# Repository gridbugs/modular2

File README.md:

# Modular 2

A modular synthesizer, where modules are designed as close to bare PCBs as is
practical/safe. This is the spiritual successor to the [briefcase modular
synthesizer](https://github.com/gridbugs/briefcase-synth/).

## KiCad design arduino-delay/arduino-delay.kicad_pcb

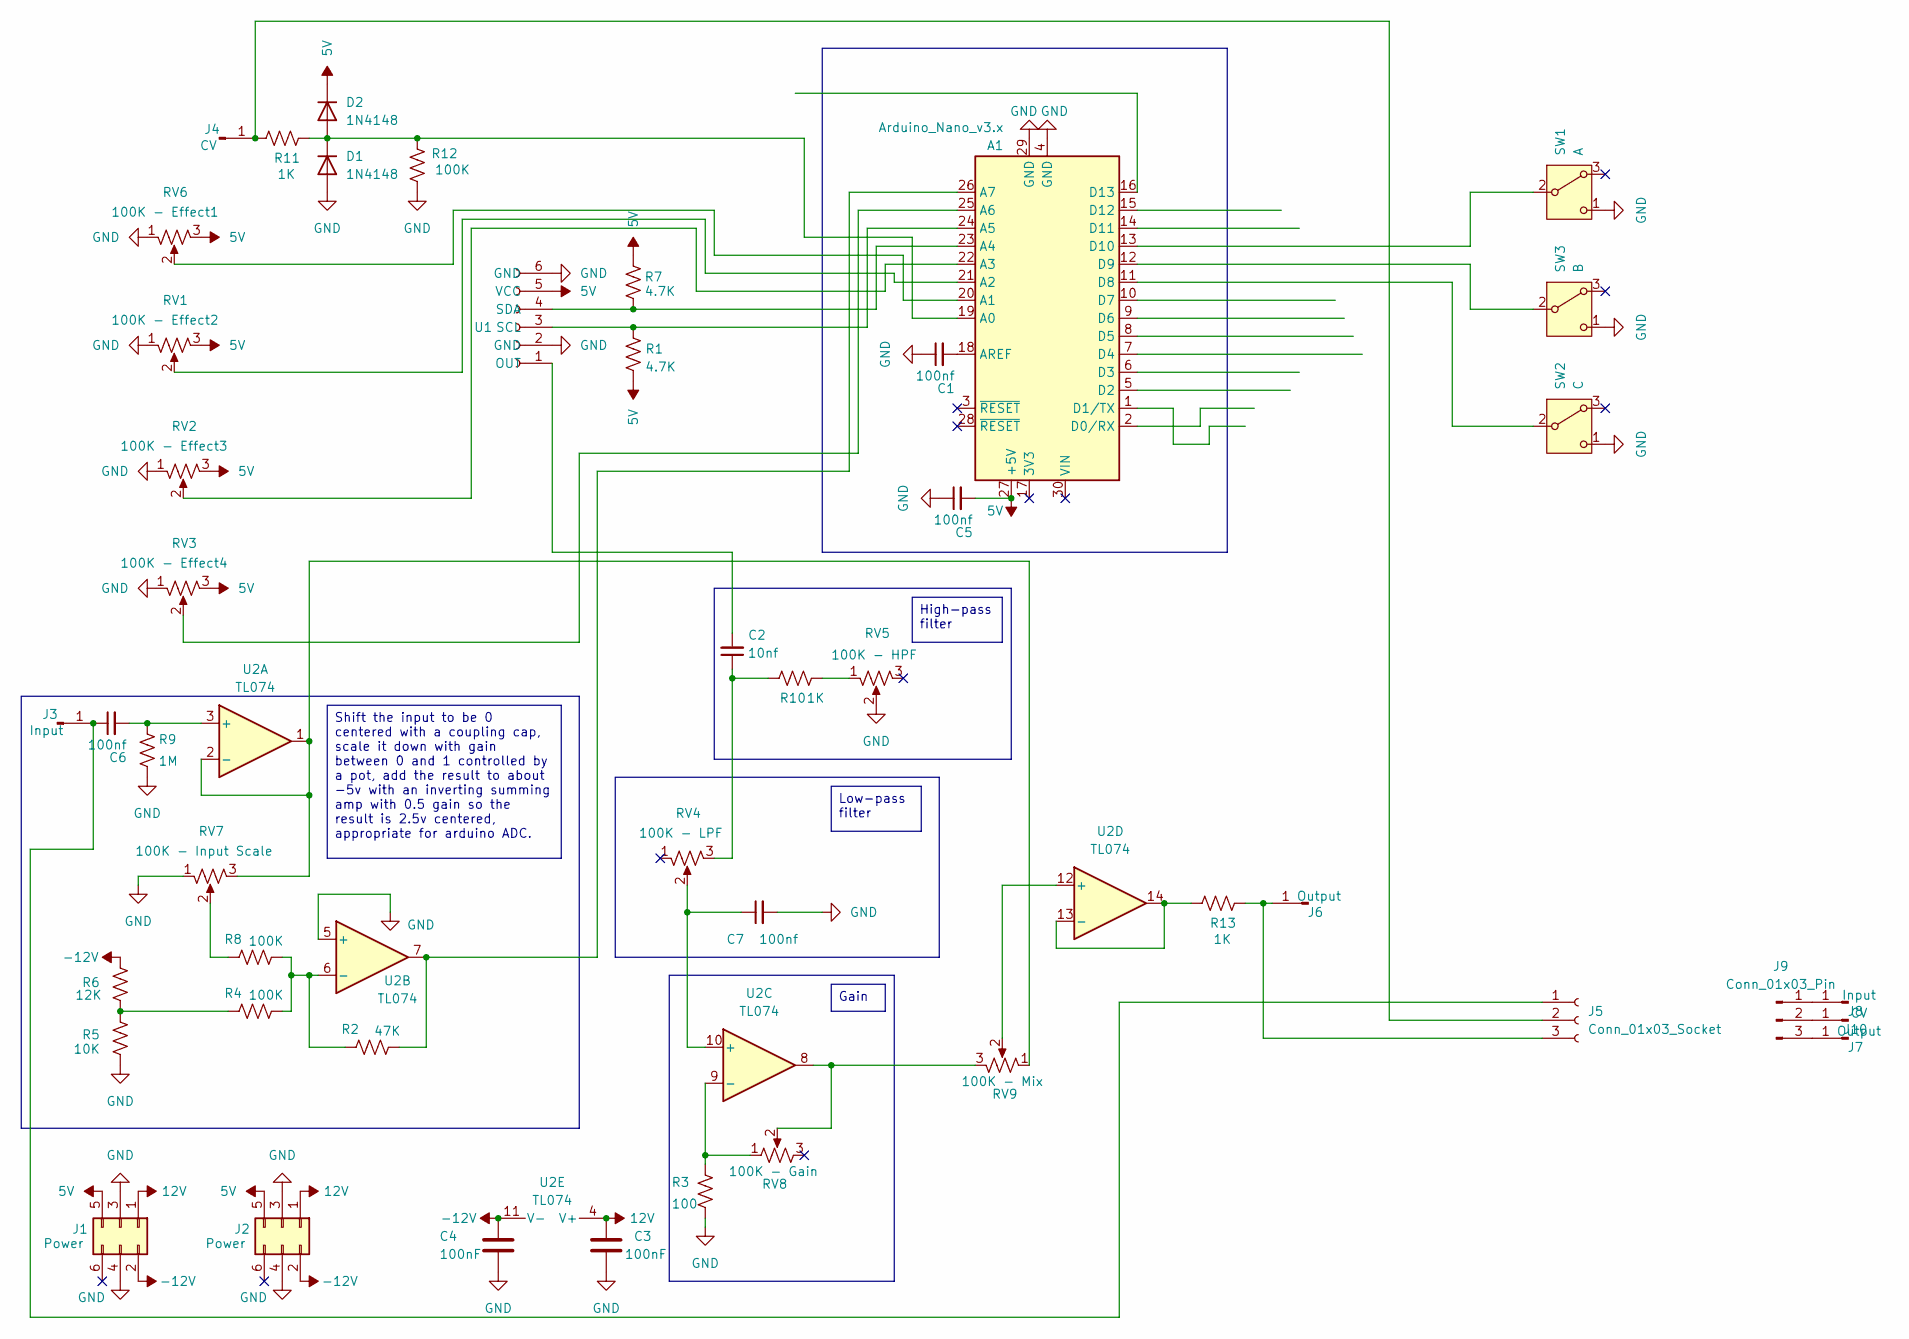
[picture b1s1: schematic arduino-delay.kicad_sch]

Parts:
A1: Arduino_Nano_v3.x; Arduino_Nano_sockets
C1, C5, C6, C7: 100nf; C_Disc_D4.3mm_W1.9mm_P5.00mm
C2: 10nf; C_Disc_D4.3mm_W1.9mm_P5.00mm
C3, C4: 100nF; C_Disc_D4.3mm_W1.9mm_P5.00mm
D1, D2: 1N4148; D_DO-35_SOD27_P7.62mm_Horizontal
J1, J2: Power; IDC-Header_2x03_P2.54mm_Vertical
J3, J8: Input; banana-jack
J4, J10: CV; banana-jack
J5: Conn_01x03_Socket; PinSocket_1x03_P2.54mm_Vertical
J6, J7: Output; banana-jack
J9: Conn_01x03_Pin; PinHeader_1x03_P2.54mm_Vertical
R1, R7: 4.7K; R_Axial_DIN0207_L6.3mm_D2.5mm_P10.16mm_Horizontal
R2: 47K; R_Axial_DIN0207_L6.3mm_D2.5mm_P10.16mm_Horizontal
R3: 100; R_Axial_DIN0207_L6.3mm_D2.5mm_P10.16mm_Horizontal
R4, R8, R12: 100K; R_Axial_DIN0207_L6.3mm_D2.5mm_P10.16mm_Horizontal
R5: 10K; R_Axial_DIN0207_L6.3mm_D2.5mm_P10.16mm_Horizontal
R6: 12K; R_Axial_DIN0207_L6.3mm_D2.5mm_P10.16mm_Horizontal
R9: 1M; R_Axial_DIN0207_L6.3mm_D2.5mm_P10.16mm_Horizontal
R10, R11, R13: 1K; R_Axial_DIN0207_L6.3mm_D2.5mm_P10.16mm_Horizontal
RV1: 100K - Effect2; Potentiometer_Alps_RK09K_Single_Vertical - knob padding
RV2: 100K - Effect3; Potentiometer_Alps_RK09K_Single_Vertical - knob padding
RV3: 100K - Effect4; Potentiometer_Alps_RK09K_Single_Vertical - knob padding
RV4: 100K - LPF; Potentiometer_Alps_RK09K_Single_Vertical - knob padding
RV5: 100K - HPF; Potentiometer_Alps_RK09K_Single_Vertical - knob padding
RV6: 100K - Effect1; Potentiometer_Alps_RK09K_Single_Vertical - knob padding
RV7: 100K - Input Scale; Potentiometer_Alps_RK09K_Single_Vertical - knob padding
RV8: 100K - Gain; Potentiometer_Alps_RK09K_Single_Vertical - knob padding
RV9: 100K - Mix; Potentiometer_Alps_RK09K_Single_Vertical - knob padding
SW1: A; switch1
SW2: C; switch1
SW3: B; switch1
U1: mcp4725_breakout
U2: TL074; DIP-14_W7.62mm_Socket

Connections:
5V: A1.27 (+5V), C5.2, D2.1 (K), J1.5, J2.5, R1.2, R7.2, RV1.3, RV2.3, RV3.3, RV6.3, U1.5 (VCC)
12V: C3.2, J1.1, J2.1, U2.4 (V+)
-12V: C4.2, J1.2, J2.2, R6.2, U2.11 (V-)
GND: A1.4 (GND), A1.29 (GND), C1.1, C3.1, C4.1, C5.1, C7.2, D1.2 (A), J1.3, J1.4, J2.3, J2.4, R3.1, R5.1, R9.2, R12.2, RV1.1, RV2.1, RV3.1, RV5.2, RV6.1, RV7.1, SW1.1 (C), SW2.1 (C), SW3.1 (C), U1.2 (GND), U1.6 (GND), U2.5 (+)
unnamed: A1.19 (A0), D1.1 (K), D2.2 (A), R11.1, R12.1
unnamed: A1.20 (A1), RV6.2
unnamed: A1.21 (A2), RV1.2
unnamed: A1.22 (A3), RV2.2
unnamed: A1.23 (A4), R7.1, U1.4 (SDA)
unnamed: A1.24 (A5), R1.1, U1.3 (SCL)
unnamed: A1.25 (A6), RV3.2
unnamed: A1.26 (A7), R2.2, U2.7
unnamed: A1.18 (AREF), C1.2
unnamed: A1.11 (D8), SW2.2 (B)
unnamed: A1.12 (D9), SW3.2 (B)
unnamed: A1.13 (D10), SW1.2 (B)
unnamed: C2.1, R10.2, RV4.3
unnamed: C6.1, J3.1, J5.1
unnamed: J4.1, J5.2, R11.2
unnamed: J5.3, J6.1, R13.1
unnamed: J7.1, J9.3
unnamed: J8.1, J9.1
unnamed: J9.2, J10.1
unnamed: R4.1, R5.2, R6.1
unnamed: R8.1, RV7.2
unnamed: R10.1, RV5.1
unnamed: RV8.2, RV9.3, U2.8
unnamed: C2.2, U1.1 (OUT)
unnamed: C6.2, R9.1, U2.3 (+)
unnamed: RV7.3, RV9.1, U2.1, U2.2 (-)
unnamed: R2.1, R4.2, R8.2, U2.6 (-)
unnamed: C7.1, RV4.2, U2.10 (+)
unnamed: R3.2, RV8.1, U2.9 (-)
unnamed: RV9.2, U2.12 (+)
unnamed: R13.2, U2.13 (-), U2.14

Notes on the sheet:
Shift the input to be 0 centered with a coupling cap, scale it down with gain between 0 and 1 controlled by a pot, add the result to about -5v with an inverting summing amp with 0.5 gain so the result is 2.5v centered, appropriate for arduino ADC.
High-pass filter
Gain
Low-pass filter

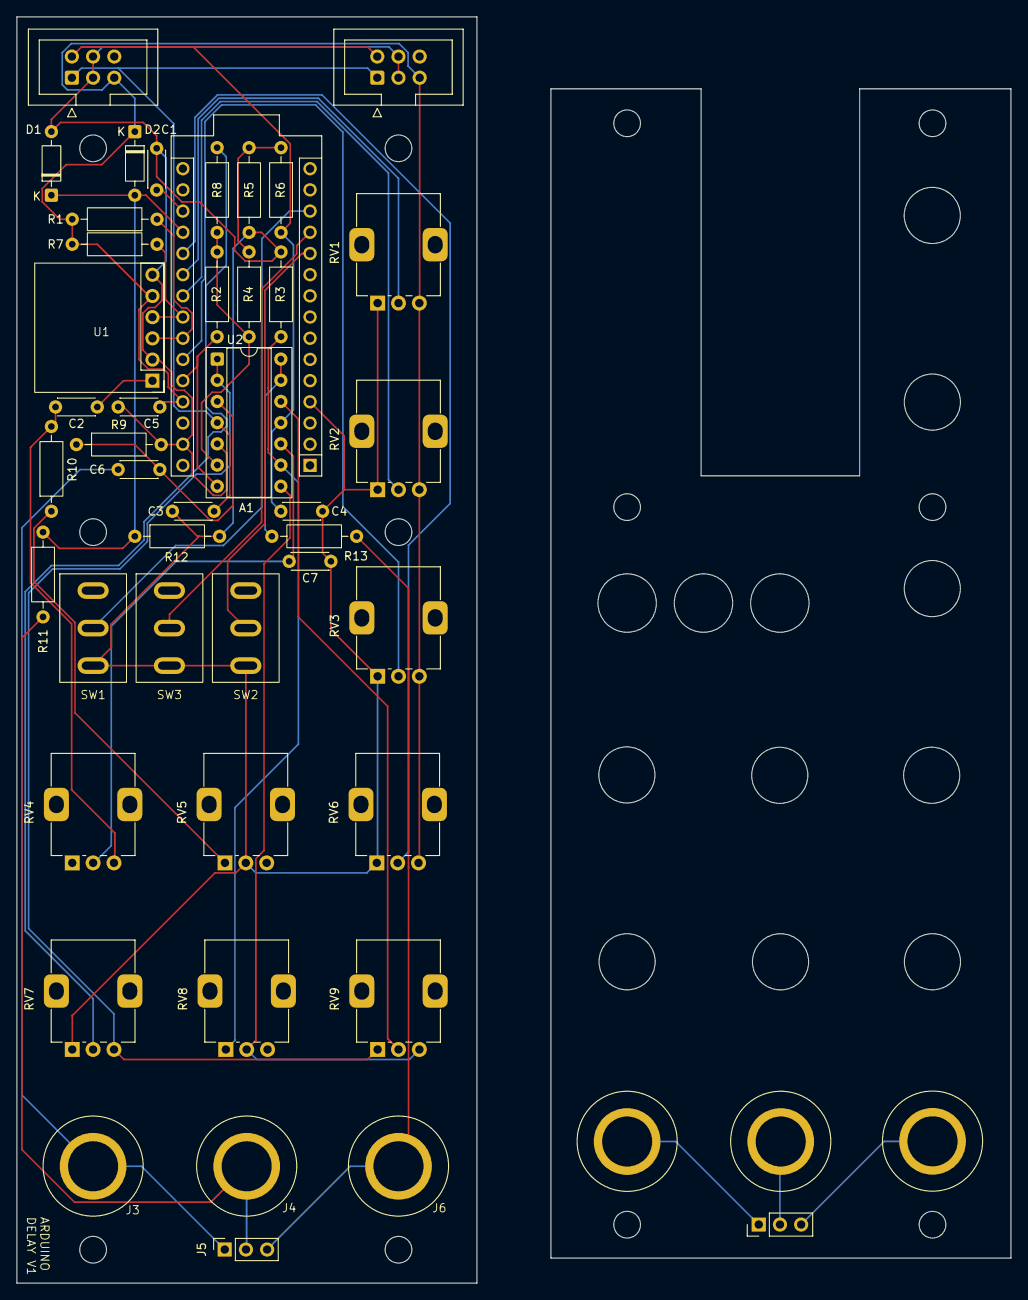
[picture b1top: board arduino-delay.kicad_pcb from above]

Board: 2 copper layers, 55.1 x 151.8 mm, 47 parts (0 on the bottom side), 35 nets.

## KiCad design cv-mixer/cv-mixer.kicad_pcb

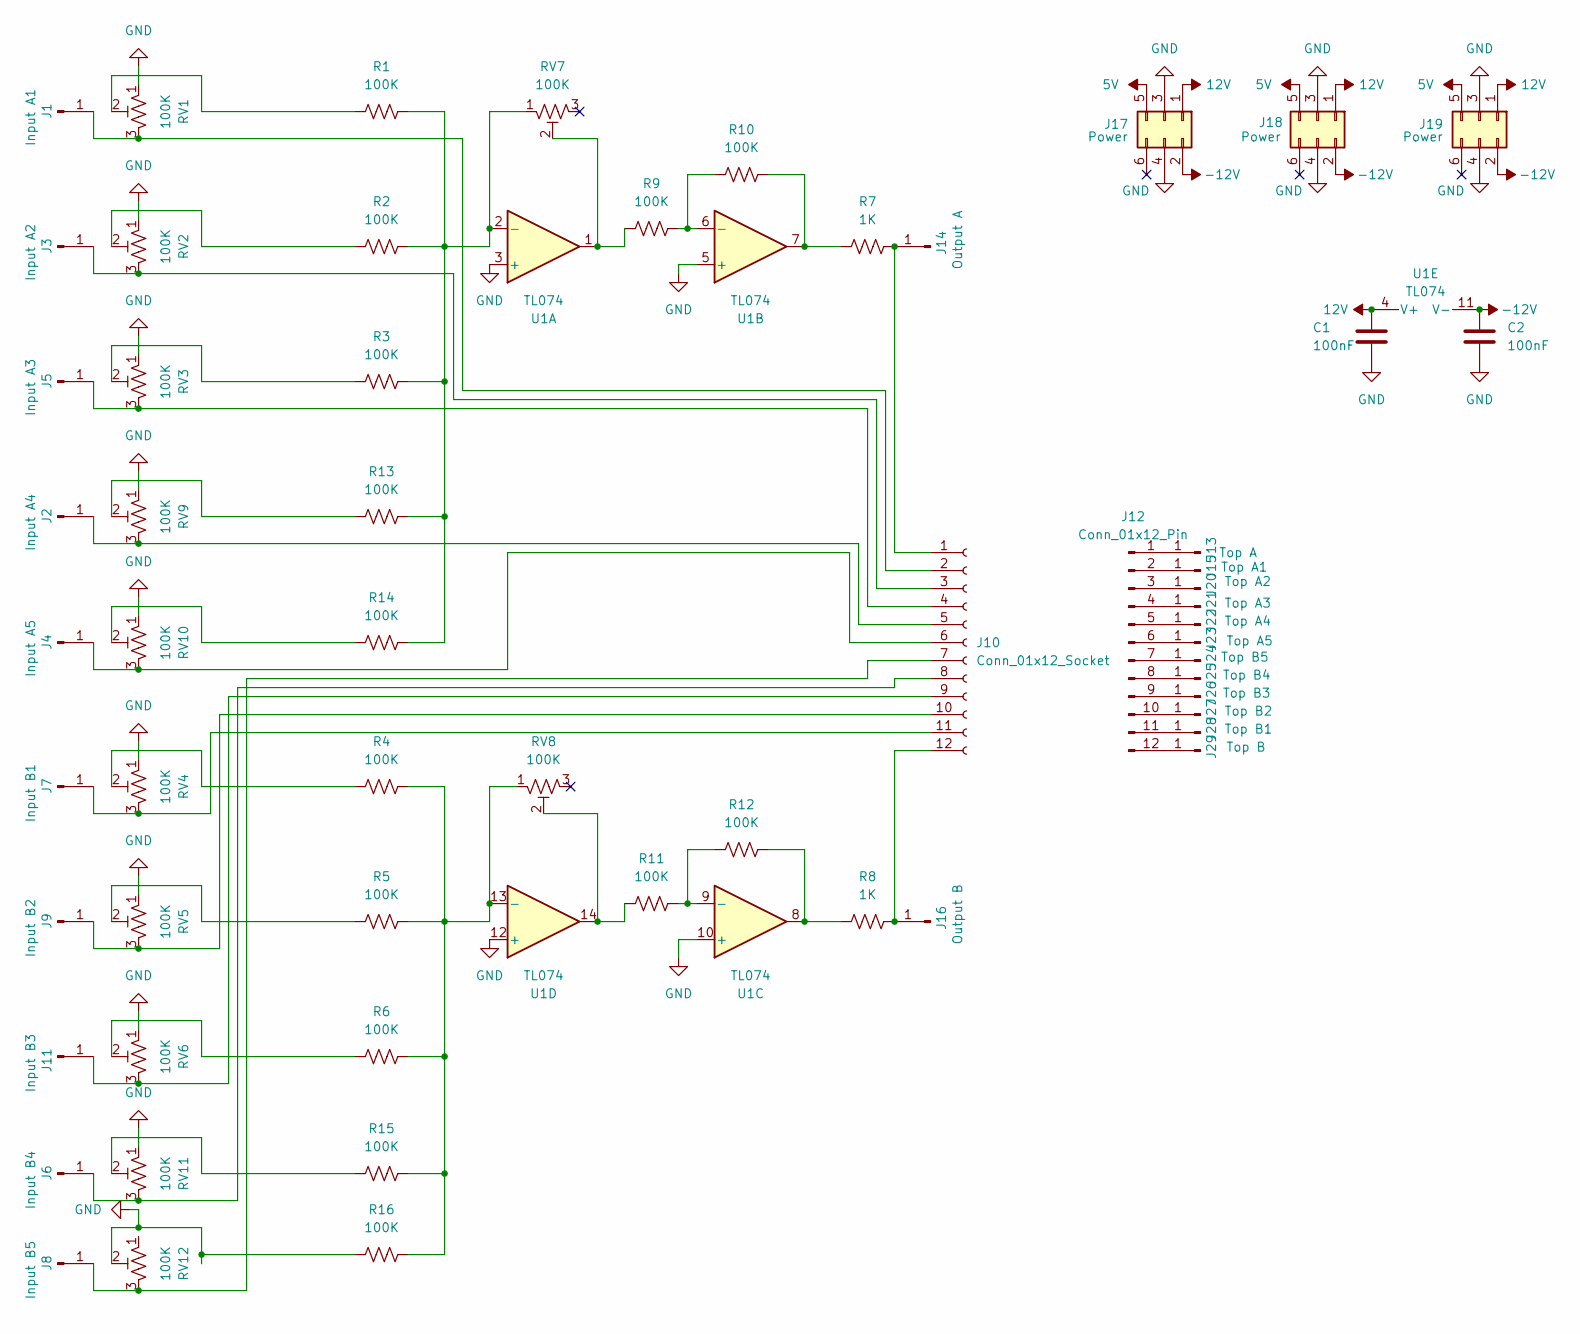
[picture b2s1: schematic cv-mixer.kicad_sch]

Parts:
C1, C2: 100nF; C_Disc_D4.3mm_W1.9mm_P5.00mm
J1: Input A1; banana-jack
J2: Input A4; banana-jack
J3: Input A2; banana-jack
J4: Input A5; banana-jack
J5: Input A3; banana-jack
J6: Input B4; banana-jack
J7: Input B1; banana-jack
J8: Input B5; banana-jack
J9: Input B2; banana-jack
J10: Conn_01x12_Socket; PinSocket_1x12_P2.54mm_Vertical
J11: Input B3; banana-jack
J12: Conn_01x12_Pin; PinHeader_1x12_P2.54mm_Vertical
J13: Top A; banana-jack
J14: Output A; banana-jack
J15: Top A1; banana-jack
J16: Output B; banana-jack
J17, J18, J19: Power; IDC-Header_2x03_P2.54mm_Vertical
J20: Top A2; banana-jack
J21: Top A3; banana-jack
J22: Top A4; banana-jack
J23: Top A5; banana-jack
J24: Top B5; banana-jack
J25: Top B4; banana-jack
J26: Top B3; banana-jack
J27: Top B2; banana-jack
J28: Top B1; banana-jack
J29: Top B; banana-jack
R1, R2, R3, R4, R5, R6, R9, R10, R11, R12, R13, R14, R15, R16: 100K; R_Axial_DIN0207_L6.3mm_D2.5mm_P10.16mm_Horizontal
R7, R8: 1K; R_Axial_DIN0207_L6.3mm_D2.5mm_P10.16mm_Horizontal
RV1, RV2, RV3, RV4, RV5, RV6, RV7, RV8, RV9, RV10, RV11, RV12: 100K; Potentiometer_Alps_RK09K_Single_Vertical - knob padding
U1: TL074; DIP-14_W7.62mm_Socket

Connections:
5V: J17.5, J18.5, J19.5
12V: C1.2, J17.1, J18.1, J19.1, U1.4 (V+)
-12V: C2.2, J17.2, J18.2, J19.2, U1.11 (V-)
GND: C1.1, C2.1, J17.3, J17.4, J18.3, J18.4, J19.3, J19.4, R16.1, RV1.1, RV2.1, RV3.1, RV4.1, RV5.1, RV6.1, RV9.1, RV10.1, RV11.1, RV12.2, U1.3 (+), U1.5 (+), U1.10 (+), U1.12 (+)
unnamed: J1.1, J10.2, RV1.3
unnamed: J10.1, J14.1, R7.2
unnamed: J3.1, J10.3, RV2.3
unnamed: J5.1, J10.4, RV3.3
unnamed: J2.1, J10.5, RV9.3
unnamed: J4.1, J10.6, RV10.3
unnamed: J8.1, J10.7, RV12.3
unnamed: J6.1, J10.8, RV11.3
unnamed: J10.9, J11.1, RV6.3
unnamed: J9.1, J10.10, RV5.3
unnamed: J7.1, J10.11, RV4.3
unnamed: J10.12, J16.1, R8.2
unnamed: J12.1, J13.1
unnamed: J12.2, J15.1
unnamed: J12.3, J20.1
unnamed: J12.4, J21.1
unnamed: J12.5, J22.1
unnamed: J12.6, J23.1
unnamed: J12.7, J24.1
unnamed: J12.8, J25.1
unnamed: J12.9, J26.1
unnamed: J12.10, J27.1
unnamed: J12.11, J28.1
unnamed: J12.12, J29.1
unnamed: R1.1, RV1.2
unnamed: R2.1, RV2.2
unnamed: R3.1, RV3.2
unnamed: R4.1, RV4.2
unnamed: R5.1, RV5.2
unnamed: R6.1, RV6.2
unnamed: R9.1, RV7.2, U1.1
unnamed: R7.1, R10.2, U1.7
unnamed: R11.1, RV8.2, U1.14
unnamed: R8.1, R12.2, U1.8
unnamed: R13.1, RV9.2
unnamed: R14.1, RV10.2
unnamed: R15.1, RV11.2
unnamed: R1.2, R2.2, R3.2, R13.2, R14.2, RV7.1, U1.2 (-)
unnamed: R9.2, R10.1, U1.6 (-)
unnamed: R11.2, R12.1, U1.9 (-)
unnamed: R4.2, R5.2, R6.2, R15.2, R16.2, RV8.1, U1.13 (-)

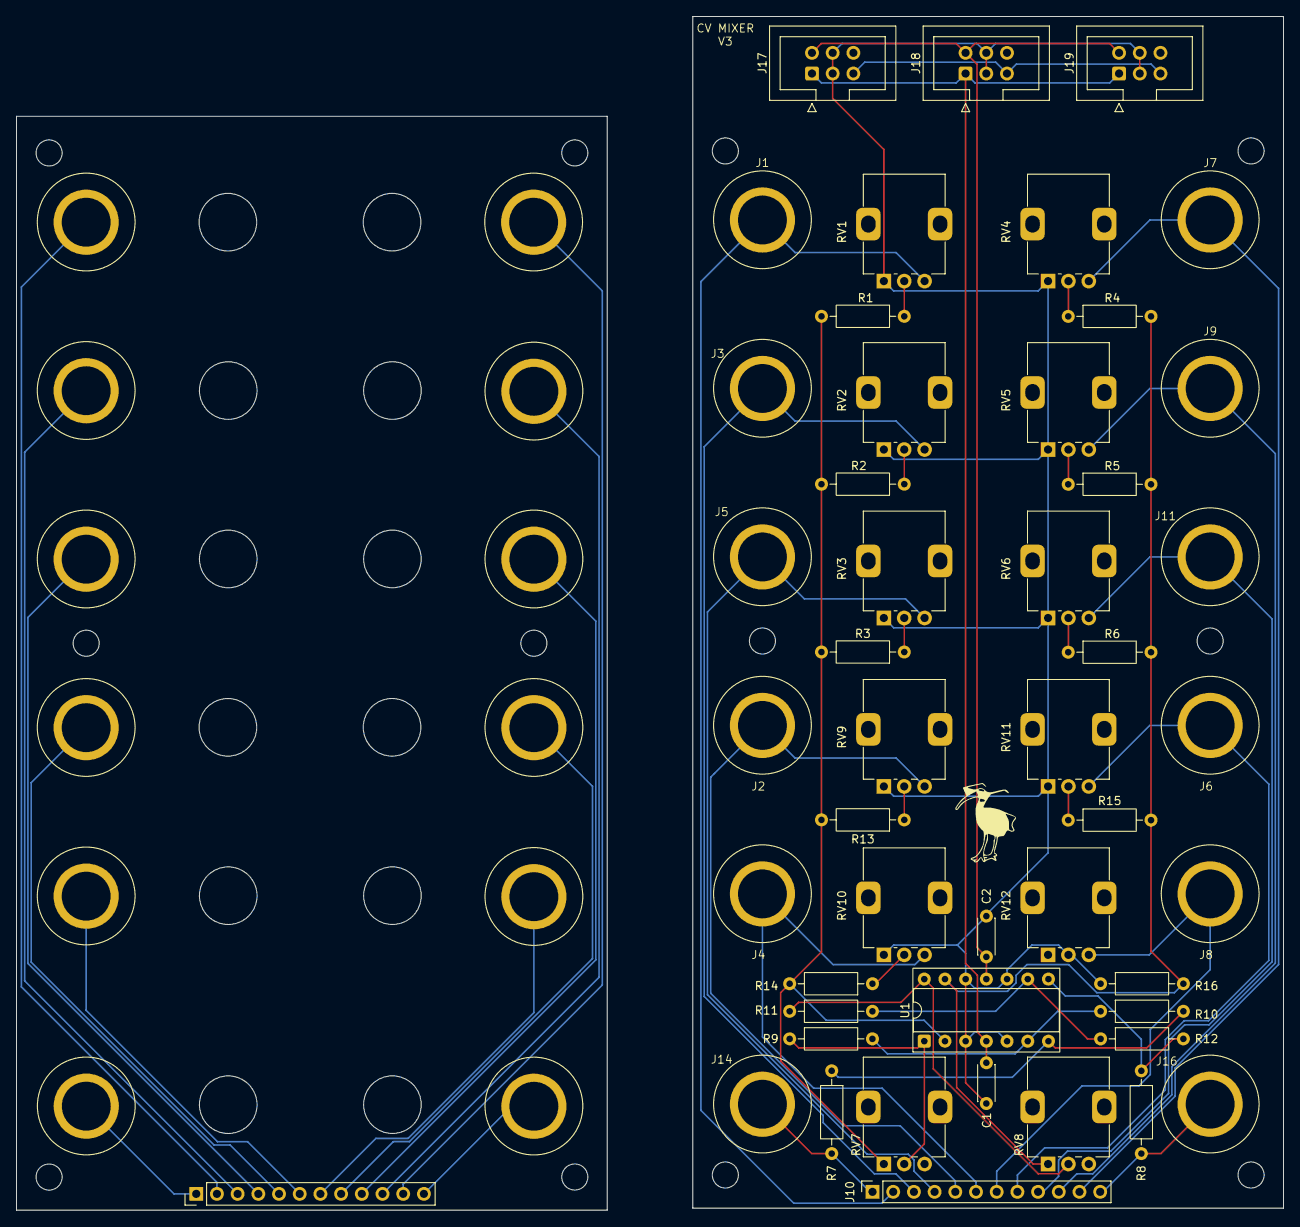
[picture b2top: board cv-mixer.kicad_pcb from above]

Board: 2 copper layers, 155.5 x 146.5 mm, 60 parts (0 on the bottom side), 45 nets.

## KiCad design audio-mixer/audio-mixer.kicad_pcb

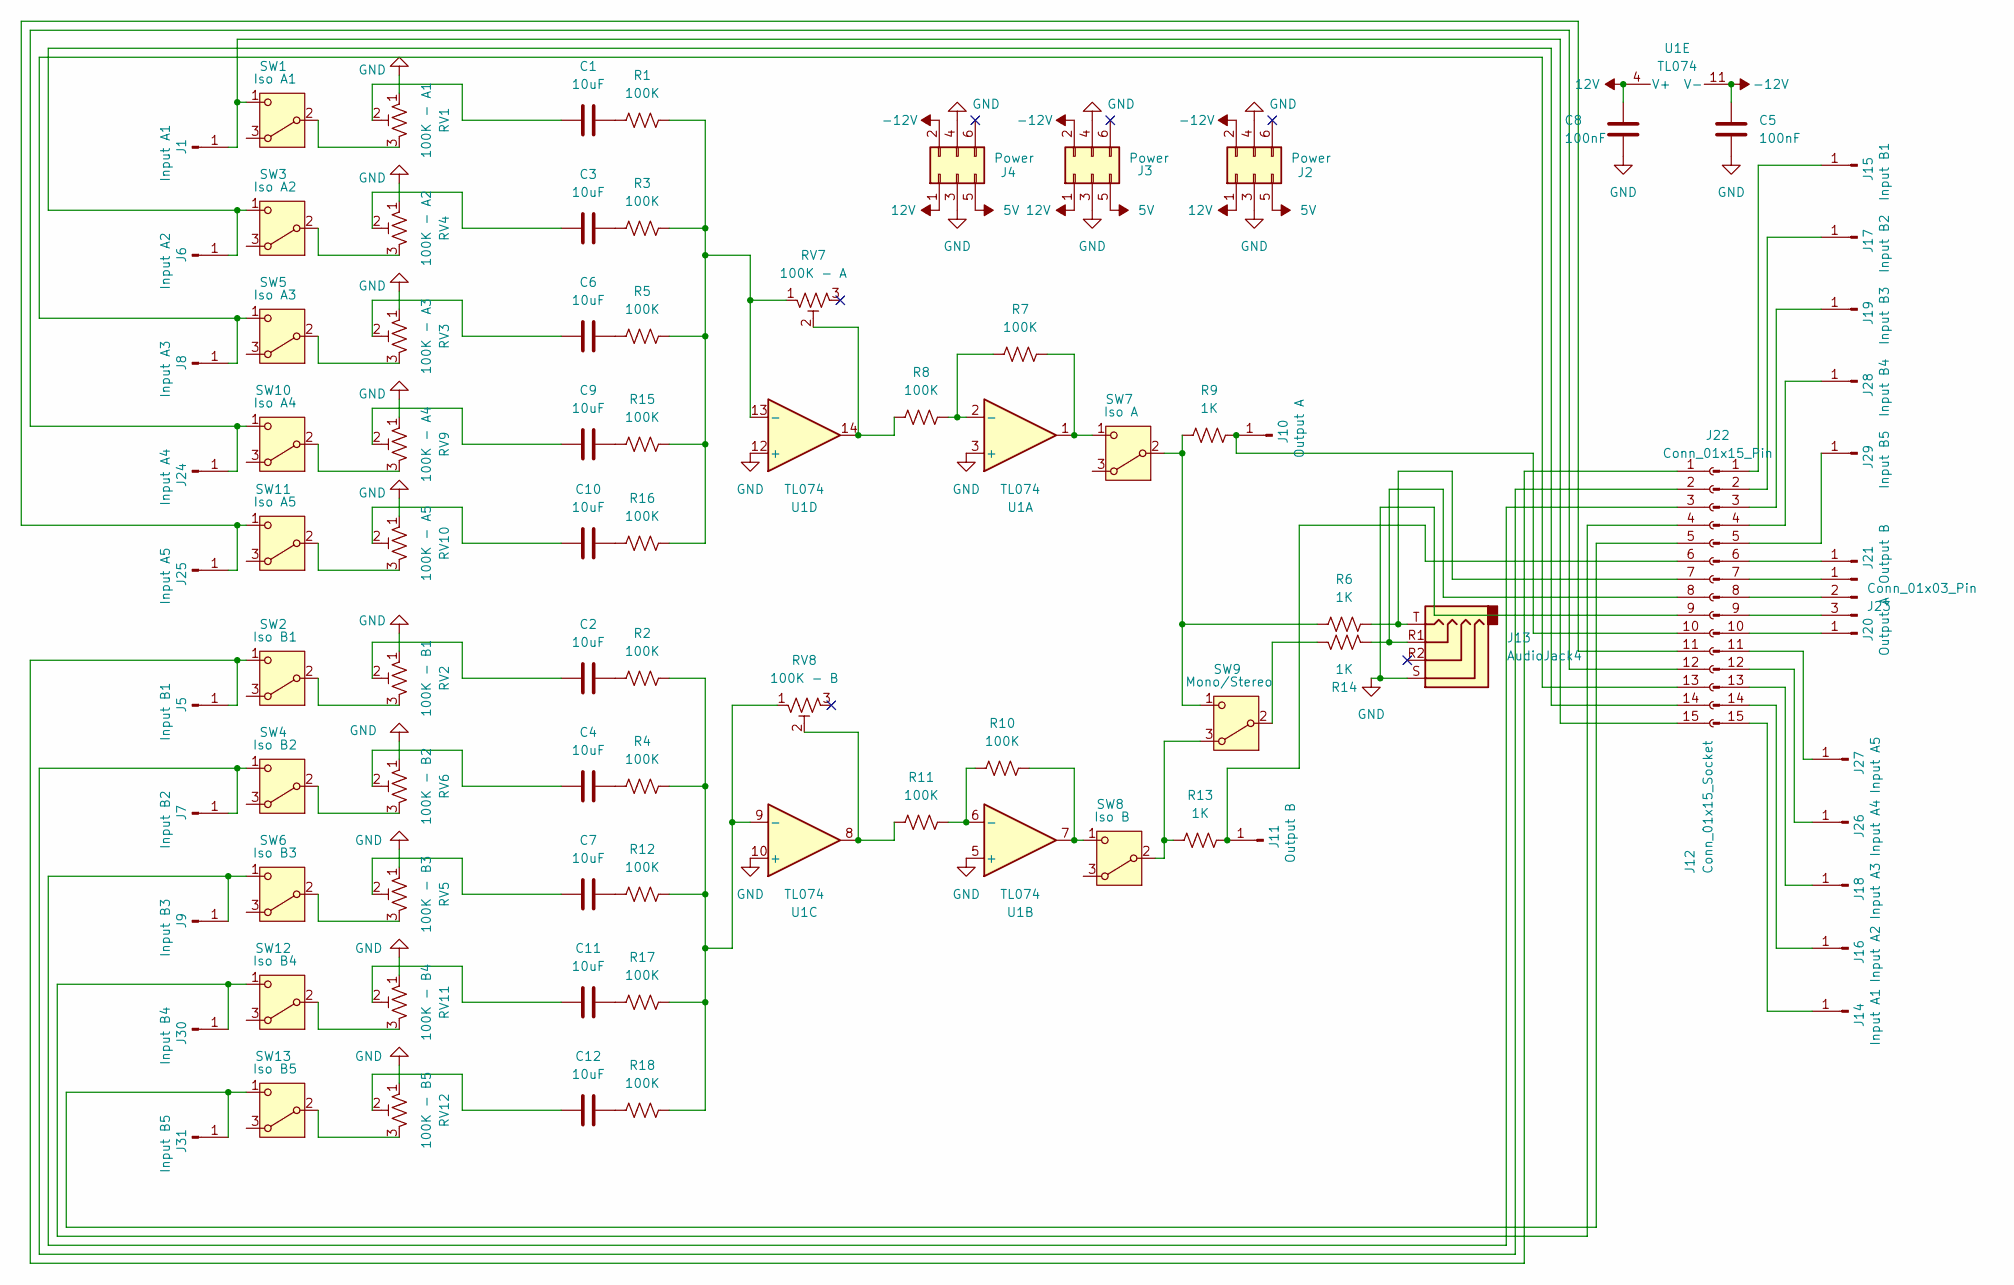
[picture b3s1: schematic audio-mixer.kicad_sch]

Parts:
C1, C2, C3, C4, C6, C7, C9, C10, C11, C12: 10uF; C_Disc_D4.3mm_W1.9mm_P5.00mm
C5, C8: 100nF; C_Disc_D4.3mm_W1.9mm_P5.00mm
J1, J14: Input A1; banana-jack
J2, J3, J4: Power; IDC-Header_2x03_P2.54mm_Vertical
J5, J15: Input B1; banana-jack
J6, J16: Input A2; banana-jack
J7, J17: Input B2; banana-jack
J8, J18: Input A3; banana-jack
J9, J19: Input B3; banana-jack
J10, J20: Output A; banana-jack
J11, J21: Output B; banana-jack
J12: Conn_01x15_Socket; PinSocket_1x15_P2.54mm_Vertical
J13: AudioJack4; audio jack breakout
J22: Conn_01x15_Pin; PinHeader_1x15_P2.54mm_Vertical
J23: Conn_01x03_Pin; PinHeader_1x03_P2.54mm_Vertical
J24, J26: Input A4; banana-jack
J25, J27: Input A5; banana-jack
J28, J30: Input B4; banana-jack
J29, J31: Input B5; banana-jack
R1, R2, R3, R4, R5, R7, R8, R10, R11, R12, R15, R16, R17, R18: 100K; R_Axial_DIN0207_L6.3mm_D2.5mm_P10.16mm_Horizontal
R6, R9, R13, R14: 1K; R_Axial_DIN0207_L6.3mm_D2.5mm_P10.16mm_Horizontal
RV1: 100K - A1; Potentiometer_Alps_RK09K_Single_Vertical - knob padding
RV2: 100K - B1; Potentiometer_Alps_RK09K_Single_Vertical - knob padding
RV3: 100K - A3; Potentiometer_Alps_RK09K_Single_Vertical - knob padding
RV4: 100K - A2; Potentiometer_Alps_RK09K_Single_Vertical - knob padding
RV5: 100K - B3; Potentiometer_Alps_RK09K_Single_Vertical - knob padding
RV6: 100K - B2; Potentiometer_Alps_RK09K_Single_Vertical - knob padding
RV7: 100K - A; Potentiometer_Alps_RK09K_Single_Vertical - knob padding
RV8: 100K - B; Potentiometer_Alps_RK09K_Single_Vertical - knob padding
RV9: 100K - A4; Potentiometer_Alps_RK09K_Single_Vertical - knob padding
RV10: 100K - A5; Potentiometer_Alps_RK09K_Single_Vertical - knob padding
RV11: 100K - B4; Potentiometer_Alps_RK09K_Single_Vertical - knob padding
RV12: 100K - B5; Potentiometer_Alps_RK09K_Single_Vertical - knob padding
SW1: Iso A1; switch1
SW2: Iso B1; switch1
SW3: Iso A2; switch1
SW4: Iso B2; switch1
SW5: Iso A3; switch1
SW6: Iso B3; switch1
SW7: Iso A; switch1
SW8: Iso B; switch1
SW9: Mono/Stereo; switch1
SW10: Iso A4; switch1
SW11: Iso A5; switch1
SW12: Iso B4; switch1
SW13: Iso B5; switch1
U1: TL074; DIP-14_W7.62mm_Socket

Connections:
5V: J2.5, J3.5, J4.5
12V: C8.2, J2.1, J3.1, J4.1, U1.4 (V+)
-12V: C5.2, J2.2, J3.2, J4.2, U1.11 (V-)
GND: C5.1, C8.1, J2.3, J2.4, J3.3, J3.4, J4.3, J4.4, J12.9, J13.S, RV1.1, RV2.1, RV3.1, RV4.1, RV5.1, RV6.1, RV9.1, RV10.1, RV11.1, RV12.1, U1.3 (+), U1.5 (+), U1.10 (+), U1.12 (+)
unnamed: C1.1, RV1.2
unnamed: C1.2, R1.1
unnamed: C2.1, RV2.2
unnamed: C2.2, R2.1
unnamed: C3.1, RV4.2
unnamed: C3.2, R3.1
unnamed: C4.1, RV6.2
unnamed: C4.2, R4.1
unnamed: C6.1, RV3.2
unnamed: C6.2, R5.1
unnamed: C7.1, RV5.2
unnamed: C7.2, R12.1
unnamed: C9.1, RV9.2
unnamed: C9.2, R15.1
unnamed: C10.1, RV10.2
unnamed: C10.2, R16.1
unnamed: C11.1, RV11.2
unnamed: C11.2, R17.1
unnamed: C12.1, RV12.2
unnamed: C12.2, R18.1
unnamed: J1.1 (Pin_1_1), J12.15, SW1.1 (C)
unnamed: J10.1 (Pin_1_1), J12.10, R9.2
unnamed: J11.1 (Pin_1_1), J12.6, R13.2
unnamed: J5.1 (Pin_1_1), J12.1, SW2.1 (C)
unnamed: J7.1 (Pin_1_1), J12.2, SW4.1 (C)
unnamed: J9.1 (Pin_1_1), J12.3, SW6.1 (C)
unnamed: J12.4, J30.1 (Pin_1_1), SW12.1 (C)
unnamed: J12.5, J31.1 (Pin_1_1), SW13.1 (C)
unnamed: J12.7, J13.T, R6.2
unnamed: J12.8, J13.R1, R14.2
unnamed: J12.11, J25.1 (Pin_1_1), SW11.1 (C)
unnamed: J12.12, J24.1 (Pin_1_1), SW10.1 (C)
unnamed: J8.1 (Pin_1_1), J12.13, SW5.1 (C)
unnamed: J6.1 (Pin_1_1), J12.14, SW3.1 (C)
unnamed: J14.1 (Pin_1_1), J22.15
unnamed: J15.1 (Pin_1_1), J22.1
unnamed: J16.1 (Pin_1_1), J22.14
unnamed: J17.1 (Pin_1_1), J22.2
unnamed: J18.1 (Pin_1_1), J22.13
unnamed: J19.1 (Pin_1_1), J22.3
unnamed: J20.1 (Pin_1_1), J22.10
unnamed: J21.1 (Pin_1_1), J22.6
unnamed: J22.4, J28.1 (Pin_1_1)
unnamed: J22.5, J29.1 (Pin_1_1)
unnamed: J22.7, J23.1
unnamed: J22.8, J23.2
unnamed: J22.9, J23.3
unnamed: J22.11, J27.1 (Pin_1_1)
unnamed: J22.12, J26.1 (Pin_1_1)
unnamed: R8.1, RV7.2, U1.14
unnamed: R11.1, RV8.2, U1.8
unnamed: RV1.3, SW1.2 (B)
unnamed: RV2.3, SW2.2 (B)
unnamed: RV4.3, SW3.2 (B)
unnamed: RV6.3, SW4.2 (B)
unnamed: RV3.3, SW5.2 (B)
unnamed: RV5.3, SW6.2 (B)
unnamed: R6.1, R9.1, SW7.2 (B), SW9.1 (C)
unnamed: R7.2, SW7.1 (C), U1.1
unnamed: R13.1, SW8.2 (B), SW9.3 (A)
unnamed: R10.2, SW8.1 (C), U1.7
unnamed: R14.1, SW9.2 (B)
unnamed: RV9.3, SW10.2 (B)
unnamed: RV10.3, SW11.2 (B)
unnamed: RV11.3, SW12.2 (B)
unnamed: RV12.3, SW13.2 (B)
unnamed: R7.1, R8.2, U1.2 (-)
unnamed: R10.1, R11.2, U1.6 (-)
unnamed: R2.2, R4.2, R12.2, R17.2, R18.2, RV8.1, U1.9 (-)
unnamed: R1.2, R3.2, R5.2, R15.2, R16.2, RV7.1, U1.13 (-)

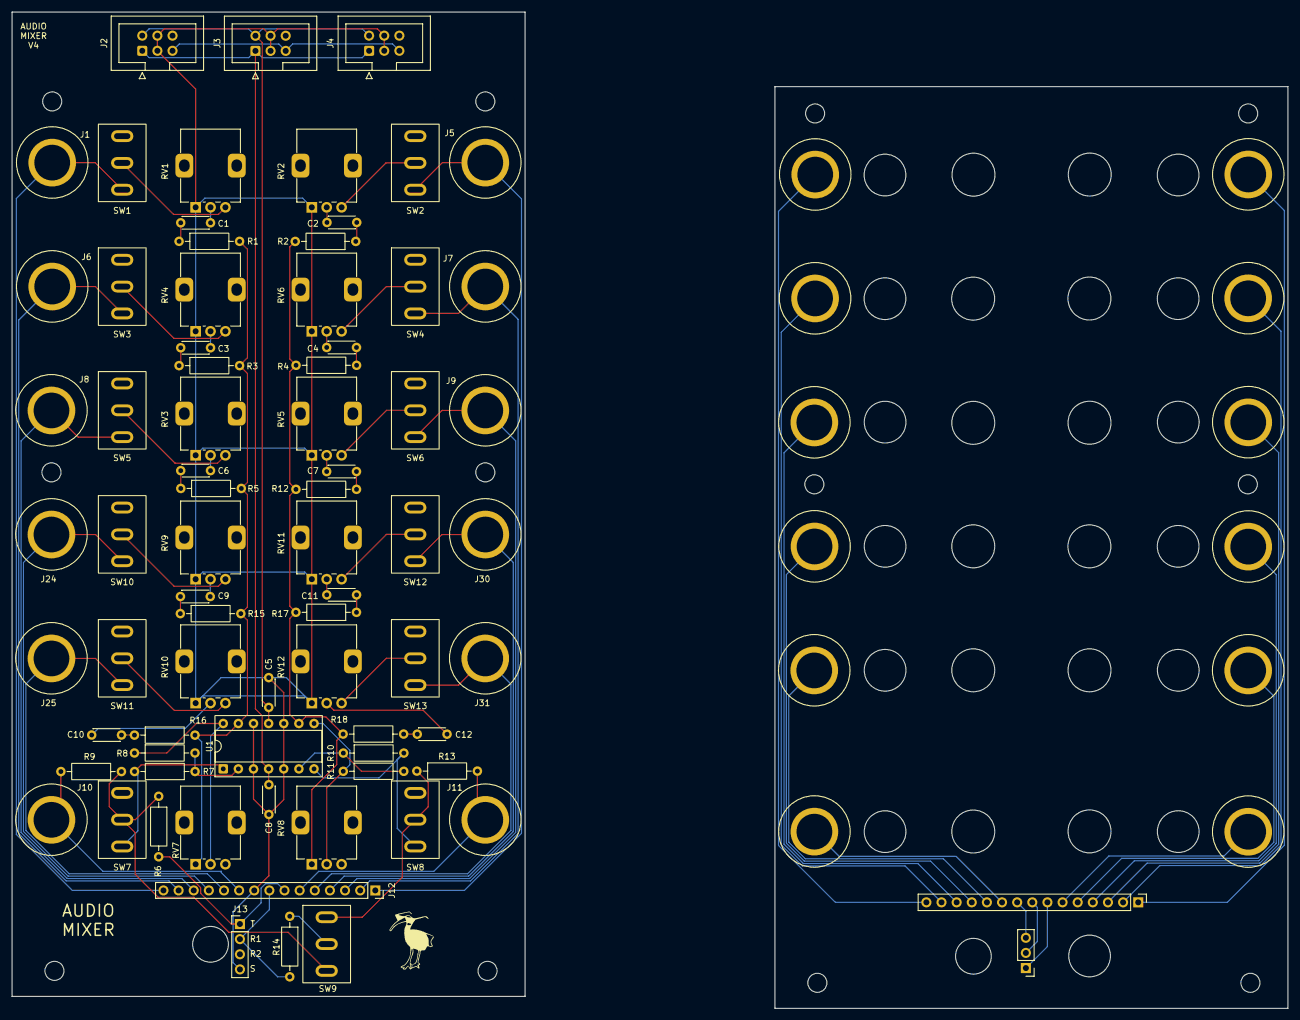
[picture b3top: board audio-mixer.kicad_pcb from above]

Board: 2 copper layers, 86.1 x 165.2 mm, 87 parts (0 on the bottom side), 74 nets.

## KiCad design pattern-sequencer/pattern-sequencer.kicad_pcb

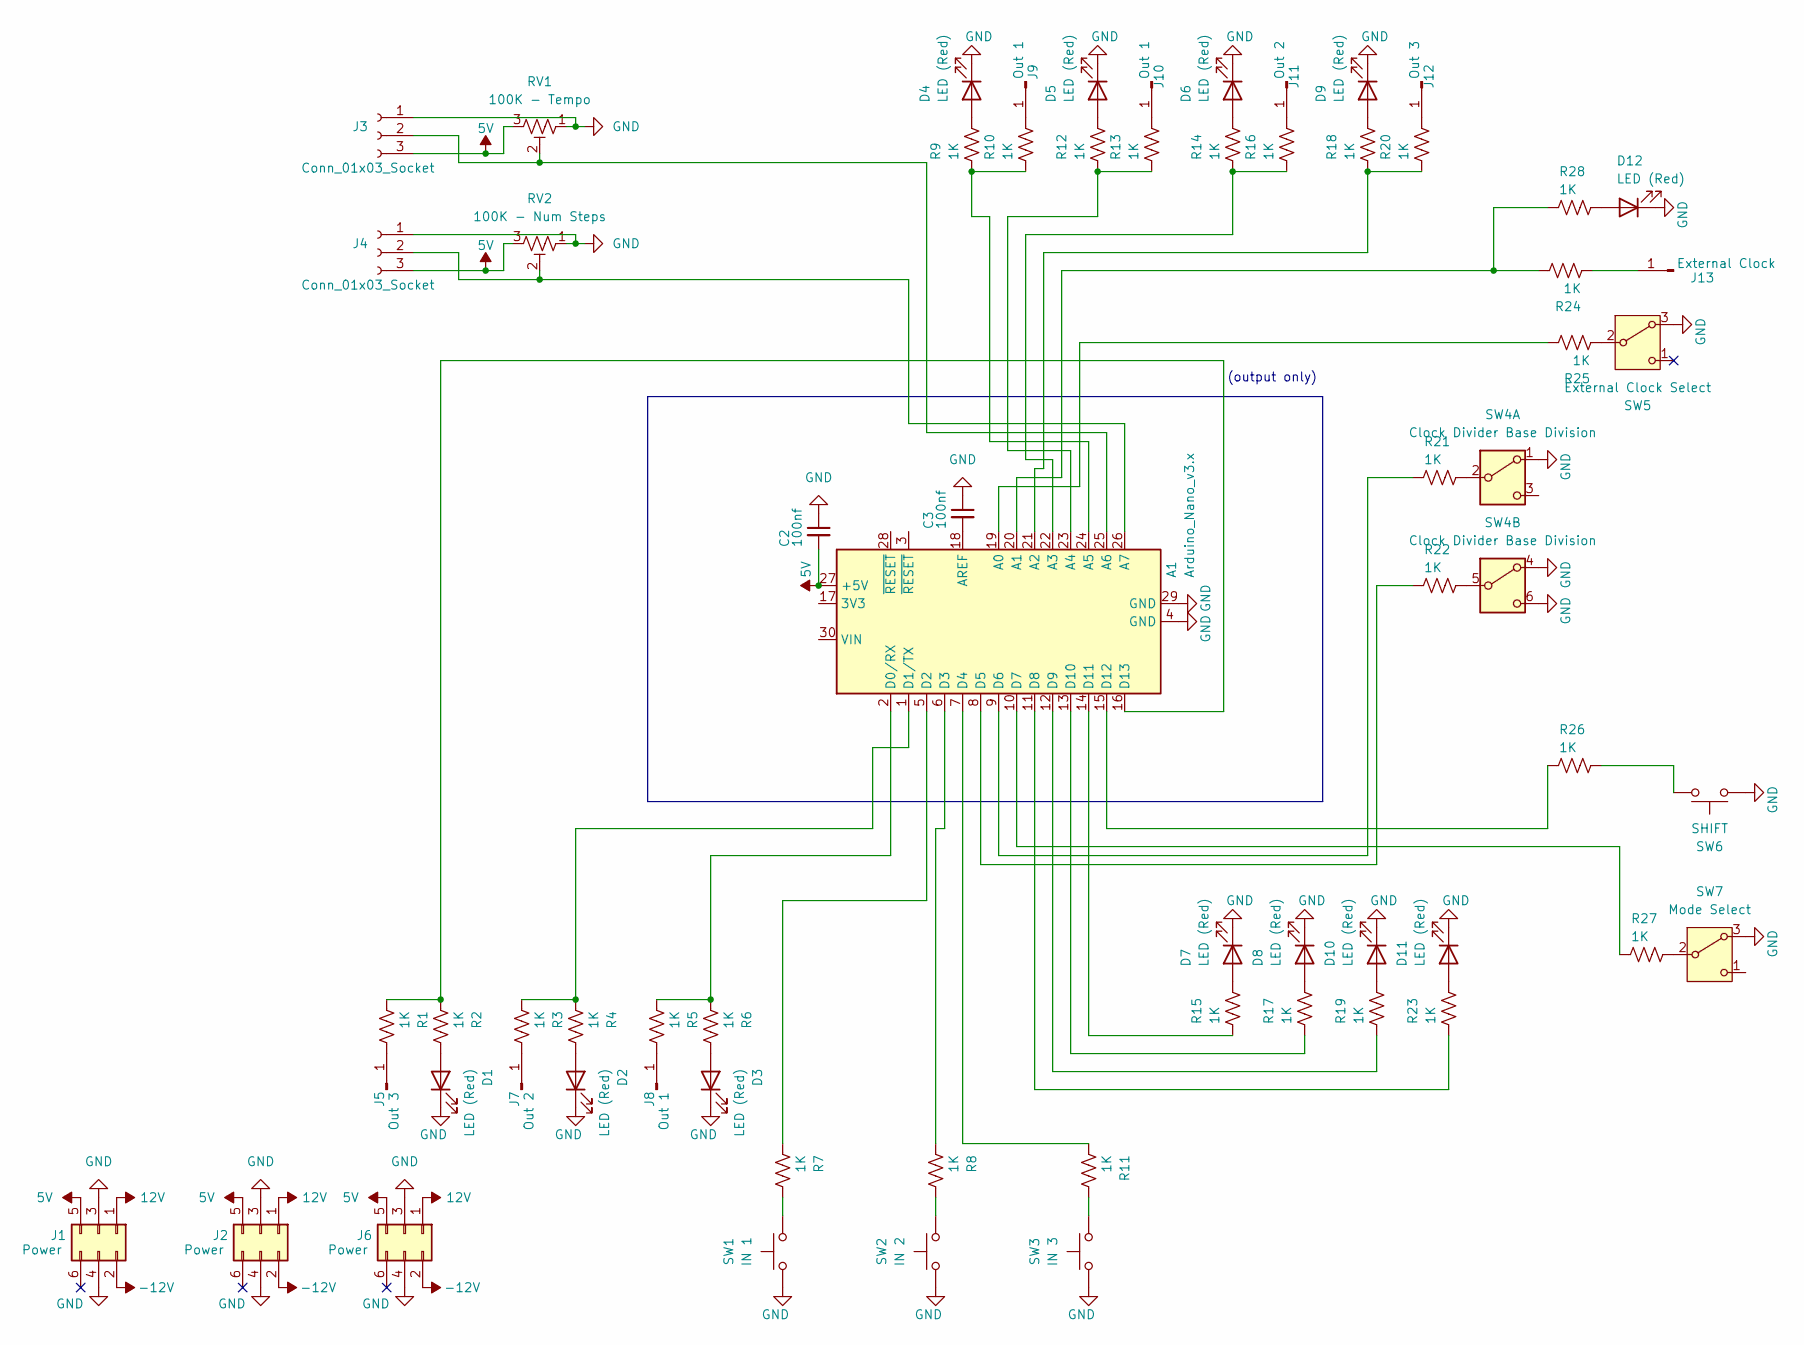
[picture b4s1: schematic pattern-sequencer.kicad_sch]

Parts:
A1: Arduino_Nano_v3.x; Arduino_Nano
C2, C3: 100nf; C_Disc_D4.3mm_W1.9mm_P5.00mm
D1, D2, D3, D4, D5, D6, D7, D8, D9, D10, D11, D12: LED (Red); LED_D5.0mm
J1, J2, J6: Power; IDC-Header_2x03_P2.54mm_Vertical
J3, J4: Conn_01x03_Socket; pot
J5, J12: Out 3; banana-jack
J7, J11: Out 2; banana-jack
J8, J9, J10: Out 1; banana-jack
J13: External Clock; banana-jack
R1, R2, R3, R4, R5, R6, R7, R8, R9, R10, R11, R12, R13, R14, R15, R16, R17, R18, R19, R20, R21, R22, R23, R24, R25, R26, R27, R28: 1K; R_Axial_DIN0207_L6.3mm_D2.5mm_P10.16mm_Horizontal
RV1: 100K - Tempo; pot-socket
RV2: 100K - Num Steps; pot-socket
SW1: IN 1; SW_Cherry_MX_1.00u_PCB
SW2: IN 2; SW_Cherry_MX_1.00u_PCB
SW3: IN 3; SW_Cherry_MX_1.00u_PCB
SW4: Clock Divider Base Division; switch2
SW5: External Clock Select; switch1
SW6: SHIFT; SW_Cherry_MX_1.00u_PCB
SW7: Mode Select; switch1

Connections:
5V: A1.27 (+5V), C2.2, J1.5, J2.5, J3.3, J4.3, J6.5, RV1.3, RV2.3
12V: J1.1, J2.1, J6.1
-12V: J1.2, J2.2, J6.2
GND: A1.4 (GND), A1.29 (GND), C2.1, C3.1, D1.1 (K), D2.1 (K), D3.1 (K), D4.1 (K), D5.1 (K), D6.1 (K), D7.1 (K), D8.1 (K), D9.1 (K), D10.1 (K), D11.1 (K), D12.1 (K), J1.3, J1.4, J2.3, J2.4, J3.1, J4.1, J6.3, J6.4, RV1.1, RV2.1, SW1.1, SW2.1, SW3.1, SW4.1 (A), SW4.4 (A), SW4.6 (C), SW5.3 (A), SW6.1, SW7.3 (A)
unnamed: A1.19 (A0), R25.1
unnamed: A1.20 (A1), R24.1, R28.2
unnamed: A1.21 (A2), R18.2, R20.2
unnamed: A1.22 (A3), R14.2, R16.2
unnamed: A1.23 (A4), R12.2, R13.2
unnamed: A1.24 (A5), R9.2, R10.2
unnamed: A1.25 (A6), J3.2, RV1.2
unnamed: A1.26 (A7), J4.2, RV2.2
unnamed: A1.18 (AREF), C3.2
unnamed: A1.2 (D0/RX), R5.2, R6.2
unnamed: A1.1 (D1/TX), R3.2, R4.2
unnamed: A1.5 (D2), R7.2
unnamed: A1.6 (D3), R8.2
unnamed: A1.7 (D4), R11.2
unnamed: A1.8 (D5), R22.2
unnamed: A1.9 (D6), R21.2
unnamed: A1.10 (D7), R27.2
unnamed: A1.11 (D8), R23.2
unnamed: A1.12 (D9), R19.2
unnamed: A1.13 (D10), R17.2
unnamed: A1.14 (D11), R15.2
unnamed: A1.15 (D12), R26.2
unnamed: A1.16 (D13), R1.2, R2.2
unnamed: D1.2 (A), R2.1
unnamed: D2.2 (A), R4.1
unnamed: D3.2 (A), R6.1
unnamed: D4.2 (A), R9.1
unnamed: D5.2 (A), R12.1
unnamed: D6.2 (A), R14.1
unnamed: D7.2 (A), R15.1
unnamed: D8.2 (A), R17.1
unnamed: D9.2 (A), R18.1
unnamed: D10.2 (A), R19.1
unnamed: D11.2 (A), R23.1
unnamed: D12.2 (A), R28.1
unnamed: J5.1 (Pin_1_1), R1.1
unnamed: J7.1 (Pin_1_1), R3.1
unnamed: J8.1 (Pin_1_1), R5.1
unnamed: J9.1 (Pin_1_1), R10.1
unnamed: J10.1 (Pin_1_1), R13.1
unnamed: J11.1 (Pin_1_1), R16.1
unnamed: J12.1 (Pin_1_1), R20.1
unnamed: J13.1 (Pin_1_1), R24.2
unnamed: R7.1, SW1.2
unnamed: R8.1, SW2.2
unnamed: R11.1, SW3.2
unnamed: R26.1, SW6.2
unnamed: R21.1, SW4.2 (B)
unnamed: R22.1, SW4.5 (B)
unnamed: R25.2, SW5.2 (B)
unnamed: R27.1, SW7.2 (B)

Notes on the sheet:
(output only)
